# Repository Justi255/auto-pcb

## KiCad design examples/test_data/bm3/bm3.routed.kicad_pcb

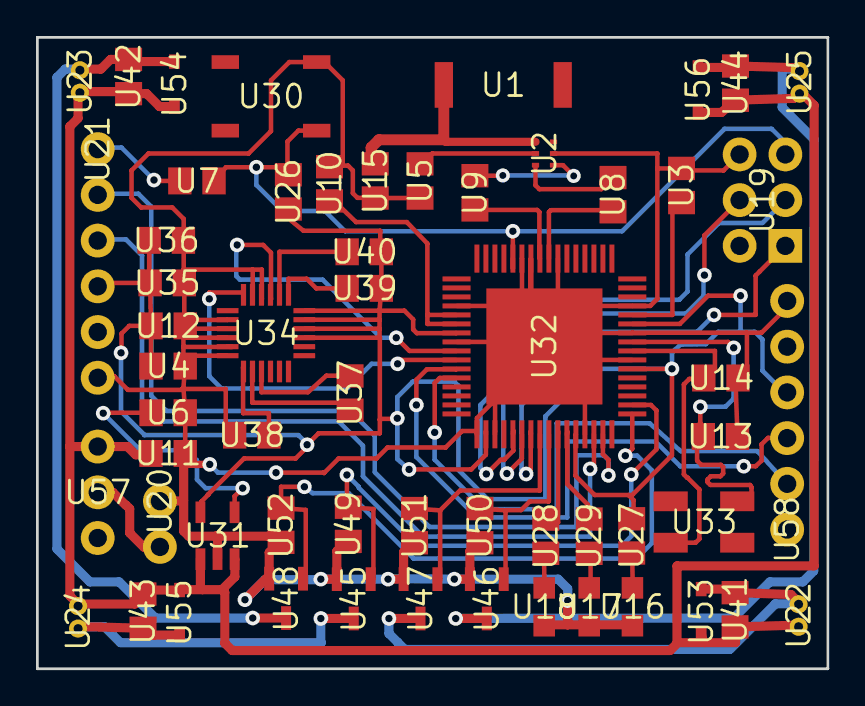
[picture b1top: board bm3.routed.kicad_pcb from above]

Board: 2 copper layers, 43.9 x 35.1 mm, 58 parts (0 on the bottom side), 44 nets.

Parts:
U1: ANTENNA-CHIP5
U2: BALUN-0805
U3, U4, U5, U6, U7, U8, U9, U10, U11, U12, U13, U14, U15, U35, U36, U37, U38, U41, U42, U43, U44: C0805
U16, U17, U18: CHIP-LED0805
U19: 2X3-NS
U20: 1X02
U21, U58: FTDI_BASIC
U22, U23, U24, U25: 653002114822
U26, U27, U28, U29, U39, U40, U49, U50, U51, U52: R0805
U30: TACTILE_SWITCH_SMD
U31: SOT23-DBV
U32: QFN-64
U33: CRYSTAL-SMD-5X3
U34: LGA-24
U45, U46, U47, U48: CONTROLLER_SOT95P237X112-3N
U53, U54, U55, U56: SOD323_ST
U57: SWITCH-SPDT

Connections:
3.3V: U4.1, U12.1, U21.VCC, U26.2, U27.2, U31.5, U32.23, U32.34, U32.44, U32.54, U32.59, U34.15, U34.16, U34.17, U34.18, U35.1, U36.1, U39.2, U40.2, U58.VCC
/MISO: U19.1, U32.39
/MOSI: U19.4, U32.38
/PB4: U32.40, U47.1, U51.1
/PB5: U32.41, U46.1, U50.1
/PB6: U28.2, U32.42
/PB7: U29.2, U32.43
/PE3: U32.49, U48.1, U52.1
/PE4: U32.50, U45.1, U49.1
/RESET: U7.2, U19.5, U26.1, U30.1, U32.12
/RFANT: U1.FEED, U2.1, U15.2
/RX0: U21.TXO, U32.46
/RX1: U32.27, U58.TXO
/SCK: U19.3, U32.37
/SCL: U32.25, U34.21
/SDA: U32.26, U34.24
/TX0: U21.RXI, U32.47
/TX1: U32.28, U58.RXI
/VBAT: U11.1, U22.1, U23.1, U24.1, U25.1, U31.1, U31.3, U41.1, U42.1, U43.1, U44.1, U53.C, U54.C, U55.C, U56.C, U57.3
GND: U2.5, U3.2, U4.2, U5.2, U6.2, U10.2, U11.2, U12.2, U13.2, U14.2, U15.1, U16.C, U17.C, U18.C, U19.6, U20.1, U21.GND, U30.3, U31.2, U32.7, U32.10, U32.11, U32.20, U32.24, U32.33, U32.35, U32.45, U32.55, U32.58, U32.61, U32.65, U34.2, U34.3, U34.4, U34.5, U34.6, U34.22, U34.23, U35.2, U36.2, U38.1, U45.2, U46.2, U47.2, U48.2, U49.2, U50.2, U51.2, U52.2, U58.GND
unnamed: U18.A, U28.1
unnamed: U2.2, U5.1
unnamed: U2.3, U8.2
unnamed: U2.4, U9.1
unnamed: U17.A, U29.1
unnamed: U3.1, U32.60
unnamed: U10.1, U32.21, U32.22
unnamed: U13.1, U32.57, U33.3
unnamed: U14.1, U32.56, U33.1
unnamed: U22.2, U41.2, U47.3, U53.A
unnamed: U23.2, U42.2, U48.3, U54.A
unnamed: U6.1, U31.4
unnamed: U24.2, U43.2, U45.3, U55.A
unnamed: U25.2, U44.2, U46.3, U56.A
unnamed: U7.1, U21.DTR
unnamed: U8.1, U32.8
unnamed: U9.2, U32.9
unnamed: U34.9, U37.1
unnamed: U34.8, U37.2
unnamed: U34.7, U38.2
unnamed: U20.2, U57.2
unnamed: U16.A, U27.1
unnamed: U34.19, U39.1
unnamed: U34.20, U40.1

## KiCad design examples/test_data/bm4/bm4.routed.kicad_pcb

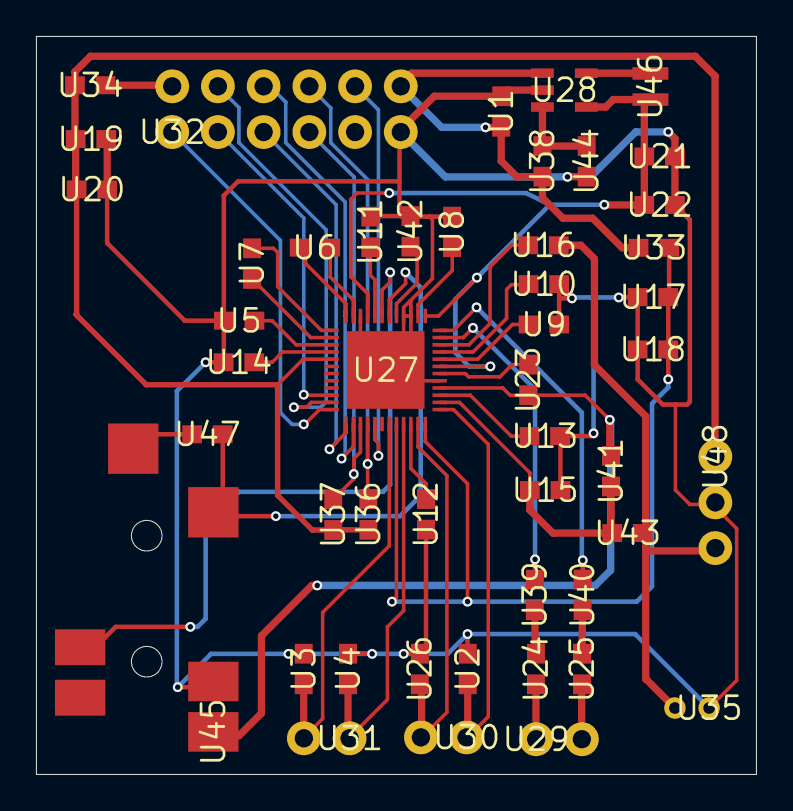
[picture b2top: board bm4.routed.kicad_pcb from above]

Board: 2 copper layers, 40.0 x 41.0 mm, 48 parts (0 on the bottom side), 47 nets.

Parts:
U1, U2, U3, U4, U5, U6, U7, U8, U9, U10, U11, U12, U13, U14, U15, U16, U17, U18, U19, U20, U21, U22, U23, U24, U25, U26, U33, U34, U36, U37, U38, U39, U40, U41, U42, U43, U44, U47: 0603
U27: QFN50P700X700X100-49N
U28: SOT95P284X122-5N
U29, U30, U31: 1X02
U32: 2X6
U35: CMC-2242PBL-A
U45: SJ-43514-SMT-TR
U46: NRH2412T2R2MNGH
U48: 1X03

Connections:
3.3V: U32.2, U34.2
5V: U1.2, U28.1, U32.12, U33.2, U38.1
/1.8VDD: U21.1, U22.1, U27.7, U27.13, U27.21, U28.4, U46.2
/3.3VDD: U19.1, U20.1, U27.29, U34.1, U36.1, U37.1, U48.1
/CPVREF: U27.17, U42.1
/HPOL: U27.18, U45.2, U47.1
/HPOR: U27.19, U45.3
/IN1P: U23.1, U27.4, U41.2, U45.1
/IN2P: U16.1, U35.2, U43.2, U48.3
/LOUTL: U27.11, U39.1
/LOUTR: U27.12, U40.1
/MICBIAS1: U15.2, U27.2, U41.1, U43.1
/SPKVDD: U17.1, U18.1, U27.44, U27.48, U33.1
/SPOLN: U26.1, U27.47, U30.2
/SPOLP: U2.1, U27.1, U30.1
/SPORN: U3.1, U27.43, U31.2
/SPORP: U4.1, U27.45, U31.1
/XADUIO_I2S0_BCLK: U27.37, U32.5
/XADUIO_I2S0_LRCKL: U27.36, U32.1
/XADUIO_SCL: U27.39, U32.7, U37.2
/XAUDIO_I2S0_DIN: U27.35, U32.4
/XAUDIO_I2S0_DOUT: U27.34, U32.3
/XAUDIO_I2S0_MCLK: U27.38, U32.6
/XAUDIO_IRQ: U27.41, U32.10
/XAUDIO_SDA: U27.40, U32.8, U36.2
GND: U1.1, U2.2, U3.2, U4.2, U5.2, U8.1, U9.1, U10.1, U11.2, U12.1, U13.1, U14.1, U15.1, U17.2, U18.2, U19.2, U20.2, U21.2, U22.2, U26.2, U27.5, U27.15, U27.16, U27.22, U27.49, U28.2, U32.11, U35.1, U42.2, U44.1, U45.4, U48.2
unnamed: U11.1, U27.20
unnamed: U23.2, U27.6
unnamed: U24.1, U39.2
unnamed: U24.2, U29.1
unnamed: U25.1, U40.2
unnamed: U25.2, U29.2
unnamed: U5.1, U27.27
unnamed: U6.1, U27.24
unnamed: U6.2, U27.23
unnamed: U7.1, U27.25
unnamed: U7.2, U27.26
unnamed: U8.2, U27.14
unnamed: U9.2, U27.8
unnamed: U10.2, U27.9
unnamed: U12.2, U27.46
unnamed: U13.2, U27.3
unnamed: U14.2, U27.28
unnamed: U16.2, U27.10
unnamed: U28.3, U38.2, U44.2
unnamed: U28.5, U46.1
unnamed: U45.5, U47.2

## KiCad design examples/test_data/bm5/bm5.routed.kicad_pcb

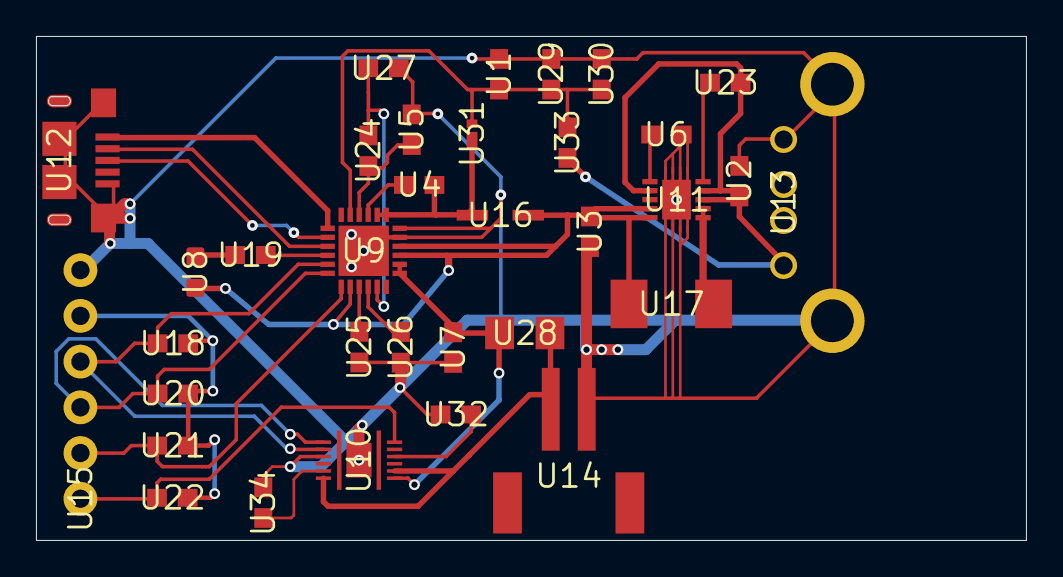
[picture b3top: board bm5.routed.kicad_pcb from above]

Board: 2 copper layers, 55.0 x 28.0 mm, 34 parts (0 on the bottom side), 27 nets.

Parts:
U1, U2, U3, U4, U5, U6, U7, U18, U19, U20, U21, U22, U23, U24, U25, U26, U27, U29, U30, U32, U33, U34: 0603
U8: LED-0603
U9: QFN50P400X400X100-25N
U10: BQ27441DRZRG1A
U11: SON50P300X300X100-11N
U12: 10118193-0001LF
U13: UE27AC54100
U14: JST-2-SMD
U15: 1X06
U16: INDPM3630X200N
U17: INDPM5552X200N
U28: 1206
U31: DSN2_1

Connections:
3.3V: U15.5, U18.2, U20.2, U21.2, U22.2
5V: U2.1, U11.3, U11.4, U11.7, U13.1, U23.1, U33.2
/CHG_INT: U9.7, U15.2, U21.1
/FUEL_INT: U10.12, U15.1, U22.1
/REG: U5.1, U9.22, U24.1
/SCL: U9.5, U10.2, U15.4, U18.1
/SDA: U9.6, U10.1, U15.3, U20.1
/VBAT_CELL: U7.1, U9.13, U9.14, U10.7, U28.1
/VBAT_MAIN: U3.1, U8.A, U9.8, U9.15, U9.16, U11.9, U11.10, U16.2, U17.1
GND: U1.2, U2.2, U3.2, U5.2, U6.2, U7.2, U9.17, U9.18, U9.25, U10.3, U10.13, U11.GND@1, U11.GND@2, U11.GND@3, U11.GND@4, U11.GND@5, U11.GND@6, U11.GND@7, U11.GND@8, U11.GND@9, U12.GND, U12.SHIELD$1, U12.SHIELD$2, U12.SHIELD$3, U12.SHIELD$4, U13.4, U13.5, U13.6, U14.1, U15.6, U25.1, U26.1, U27.1, U29.2, U30.2, U32.1, U34.2
unnamed: U4.1, U9.19, U9.20, U16.1, U31.2
unnamed: U4.2, U9.21
unnamed: U1.1, U9.23, U29.1, U30.1, U31.1, U33.1
unnamed: U6.1, U11.6
unnamed: U10.5, U34.1
unnamed: U8.C, U19.1
unnamed: U9.1, U12.VCC
unnamed: U9.2, U12.D+
unnamed: U9.3, U12.D-
unnamed: U9.4, U19.2
unnamed: U9.9, U25.2
unnamed: U9.10, U26.2
unnamed: U9.11, U24.2, U27.2
unnamed: U10.6, U10.8, U14.2, U28.2
unnamed: U10.10, U32.2
unnamed: U11.1, U11.2, U17.2
unnamed: U11.5, U23.2

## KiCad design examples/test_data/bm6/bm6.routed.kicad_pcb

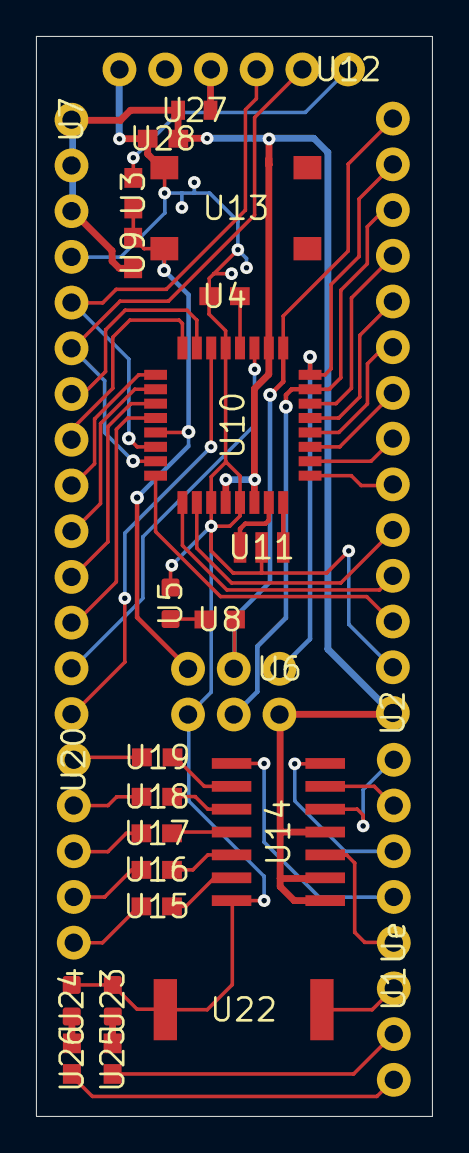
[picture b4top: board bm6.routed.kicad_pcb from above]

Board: 2 copper layers, 22.0 x 60.0 mm, 28 parts (0 on the bottom side), 51 nets.

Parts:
U1: 1X03
U2, U7: 1X14
U3, U4, U8, U9, U15, U16, U17, U18, U19, U25, U26, U28: 0603
U5, U23, U24: LED-0603
U6: 2X3
U10: TQFP32-08
U11: RESONATOR-SMD
U12: FTDI_BASIC
U13: TACTILE_SWITCH_SMD_6.2MM_TALL
U14: SO14
U20: 1X05
U22: PKMCS
U27: FUSC1608X100N
Ue: 1X05

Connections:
/A0: U7.7, U10.23
/A1: U7.8, U10.24
/A2: U7.9, U10.25
/A3: U7.10, U10.26
/A4: U7.11, U10.27
/A5: U7.12, U10.28
/A6: U7.13, U10.19
/A7: U7.14, U10.22
/D2: U2.3, U10.32
/D3: U2.4, U10.1
/D4: U2.5, U10.2
/D5: U2.6, U10.9
/D6: U2.7, U10.10
/D7: U2.8, U10.11
/D8: U2.9, U10.12
/D9: U2.10, U10.13
/D10: U2.11, U10.14
/DTR: U3.1, U12.DTR
/GO: U14.3, Ue.1
/MISO: U2.13, U6.1, U10.16
/MOSI: U2.12, U6.4, U10.15
/OUT1: U14.8, Ue.2
/OUT2: U14.7, Ue.3
/OUT3: U14.6, Ue.4
/OUT4: U14.5, Ue.5
/RST: U3.2, U6.5, U9.1, U10.29, U13.B2
/RXI: U7.5, U10.30, U12.TXO
/SCK: U2.14, U6.3, U8.1, U10.17
/TXO: U7.6, U10.31, U12.RXI
GND: U2.2, U4.2, U5.C, U6.6, U7.4, U10.3, U10.5, U10.21, U11.2, U12.GND, U13.A2, U14.14, U22.1, U23.C, U24.C, U28.2
unnamed: U4.1, U10.20
unnamed: U5.A, U8.2
unnamed: U23.A, U25.1
unnamed: U24.A, U26.1
unnamed: U12.VCC, U27.1
unnamed: U14.9, U19.2
unnamed: U14.10, U18.2
unnamed: U14.11, U17.2
unnamed: U14.12, U16.2
unnamed: U14.13, U15.2
unnamed: U19.1, U20.1
unnamed: U18.1, U20.2
unnamed: U17.1, U20.3
unnamed: U16.1, U20.4
unnamed: U15.1, U20.5
unnamed: U1.1, U22.2
unnamed: U1.2, U25.2
unnamed: U1.3, U26.2
unnamed: U10.7, U11.3
unnamed: U10.8, U11.1
VCC: U2.1, U6.2, U7.1, U7.2, U7.3, U9.2, U10.4, U10.6, U10.18, U14.1, U14.2, U14.4, U27.2, U28.1
